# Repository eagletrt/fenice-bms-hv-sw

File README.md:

# Fenice's High Voltage Battery Management System

This branch contains two projects: mainboard and cellboard.

For guidelines on how this branching system works head over to the [master's branch README](https://github.com/eagletrt/fenice-bms-hv/blob/master/README.md#repo-guidlines).

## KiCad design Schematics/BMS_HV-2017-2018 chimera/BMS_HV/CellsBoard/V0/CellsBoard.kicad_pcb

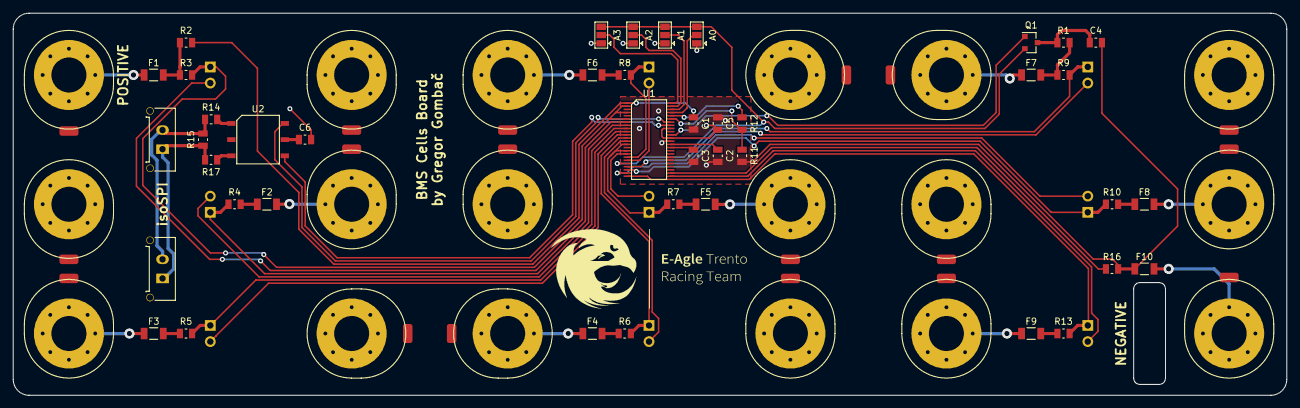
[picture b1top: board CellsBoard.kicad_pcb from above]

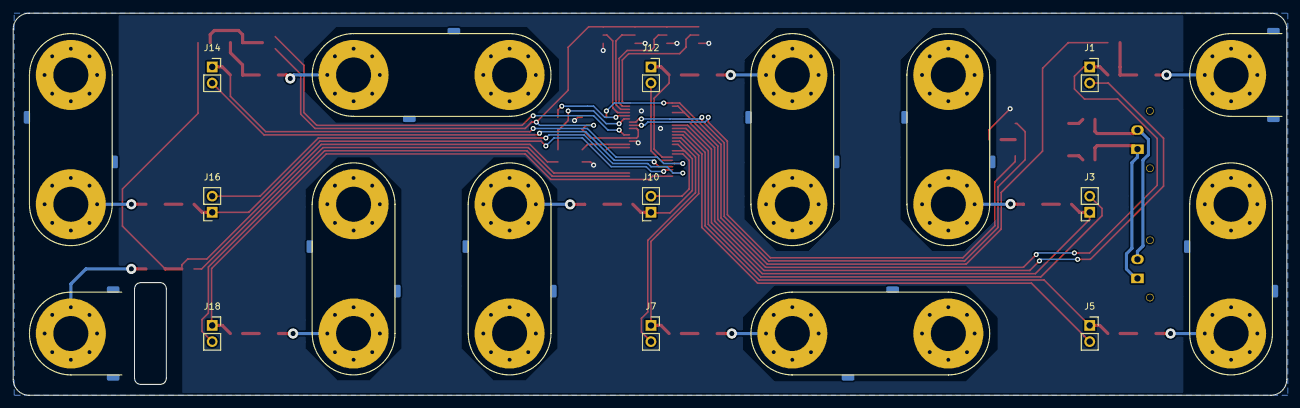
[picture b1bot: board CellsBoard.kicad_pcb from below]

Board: 2 copper layers, 200.0 x 60.0 mm, 61 parts (9 on the bottom side), 58 nets.

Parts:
C1, C4, C5: 100n; C_0805_2012Metric
C2, C3: 1u; C_0805_2012Metric
C6: 27p; C_0805_2012Metric
F1, F2, F3, F4, F5, F6, F7, F8, F9, F10: Fuse; Fuse_1206_3216Metric
J1: Temp9; PinSocket_1x02_P2.54mm_Vertical
J2: Cell9; CellEndS
J3: Temp8; PinSocket_1x02_P2.54mm_Vertical
J4: Cell8; CellShort
J5: Temp7; PinSocket_1x02_P2.54mm_Vertical
J6: Cell7; CellShort
J7: Temp6; PinSocket_1x02_P2.54mm_Vertical
J8: Cell6; CellLong
J10: Temp5; PinSocket_1x02_P2.54mm_Vertical
J11: Cell5; CellShort
J12: Temp4; PinSocket_1x02_P2.54mm_Vertical
J13: Cell4; CellShort
J14: Temp3; PinSocket_1x02_P2.54mm_Vertical
J15: Cell3; CellLong
J16: Temp2; PinSocket_1x02_P2.54mm_Vertical
J17: Cell2; CellShort
J18: Temp1; PinSocket_1x02_P2.54mm_Vertical
J19: Cell1; CellShort
J20: Cell0; CellEndD
J21, J22: isoSPI; Molex_Micro-Fit_3.0_43650-0215_1x02_P3.00mm_Vertical
JP1: A3; SolderJumper-3_P1.3mm_Open_Pad1.0x1.5mm
JP2: A2; SolderJumper-3_P1.3mm_Open_Pad1.0x1.5mm
JP3: A1; SolderJumper-3_P1.3mm_Open_Pad1.0x1.5mm
JP4: A0; SolderJumper-3_P1.3mm_Open_Pad1.0x1.5mm
Q1: BC846AW; SOT-23
R1, R2: 100R; R_0805_2012Metric
R3, R4, R5, R6, R7, R8, R9, R10, R13, R16: 330R; R_0805_2012Metric
R11: 1K4; R_0805_2012Metric
R12: 604R; R_0805_2012Metric
R14, R17: 22R; R_0805_2012Metric
R15: 120R; R_0805_2012Metric
U1: LTC6804; SSOP-48
U2: HM2103

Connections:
/0V: C1.2, C2.2, C3.2, C4.2, C5.2, C6.1, F10.2, JP1.1, JP2.1, JP3.1, JP4.1, R11.2, R16.1, U1.30, U1.31, U1.36
/A0: JP4.2, U1.45
/A1: JP3.2, U1.46
/A2: JP2.2, U1.47
/A3: JP1.2, U1.48
/C0: R16.2, U1.26
/C1: J18.1, R13.2, U1.24
/C2: J16.1, R10.2, U1.22
/C3: J14.1, R9.2, U1.20
/C4: J12.1, R8.2, U1.18
/C5: J10.1, R7.2, U1.14, U1.16
/C6: J7.1, R6.2, U1.12
/C7: J5.1, R5.2, U1.10
/C8: J3.1, R4.2, U1.8
/C9: J1.1, R3.2, U1.2, U1.4, U1.6
/CB1: F9.2, R13.1
/CB2: F8.2, R10.1
/CB3: F7.2, R1.1, R9.1
/CB4: F6.2, R8.1
/CB5: F5.2, R7.1
/CB6: F4.2, R6.1
/CB7: F3.2, R5.1
/CB8: F2.2, R4.1
/CB9: F1.2, R2.1, R3.1
/S1: J18.2, U1.25
/S2: J16.2, U1.23
/S3: J14.2, U1.21
/S4: J12.2, U1.19
/S5: J10.2, U1.17
/S6: J7.2, U1.13
/S7: J5.2, U1.11
/S8: J3.2, U1.9
/S9: J1.2, U1.7
/V+: C1.1, R2.2, U1.1
/VRef1: C2.1, U1.35
/VRef2: C3.1, U1.34
/Vreg: C5.1, JP1.3, JP2.3, JP3.3, JP4.3, Q1.2, U1.37, U1.40
/drive: Q1.1, U1.38
unnamed: C4.1, Q1.3, R1.2
unnamed: C6.2, U2.5
unnamed: F1.1, J2.1
unnamed: F2.1, J4.1
unnamed: F3.1, J6.1
unnamed: F4.1, J8.1
unnamed: F5.1, J11.1
unnamed: F6.1, J13.1
unnamed: F7.1, J15.1
unnamed: F8.1, J17.1
unnamed: F9.1, J19.1
unnamed: F10.1, J20.1
unnamed: J21.1, J22.1, R15.2, R17.2
unnamed: J21.2, J22.2, R14.2, R15.1
unnamed: R11.1, R12.2, U1.43
unnamed: R12.1, U1.44
unnamed: R14.1, U2.1
unnamed: R17.1, U2.3
unnamed: U1.41, U2.4
unnamed: U1.42, U2.6

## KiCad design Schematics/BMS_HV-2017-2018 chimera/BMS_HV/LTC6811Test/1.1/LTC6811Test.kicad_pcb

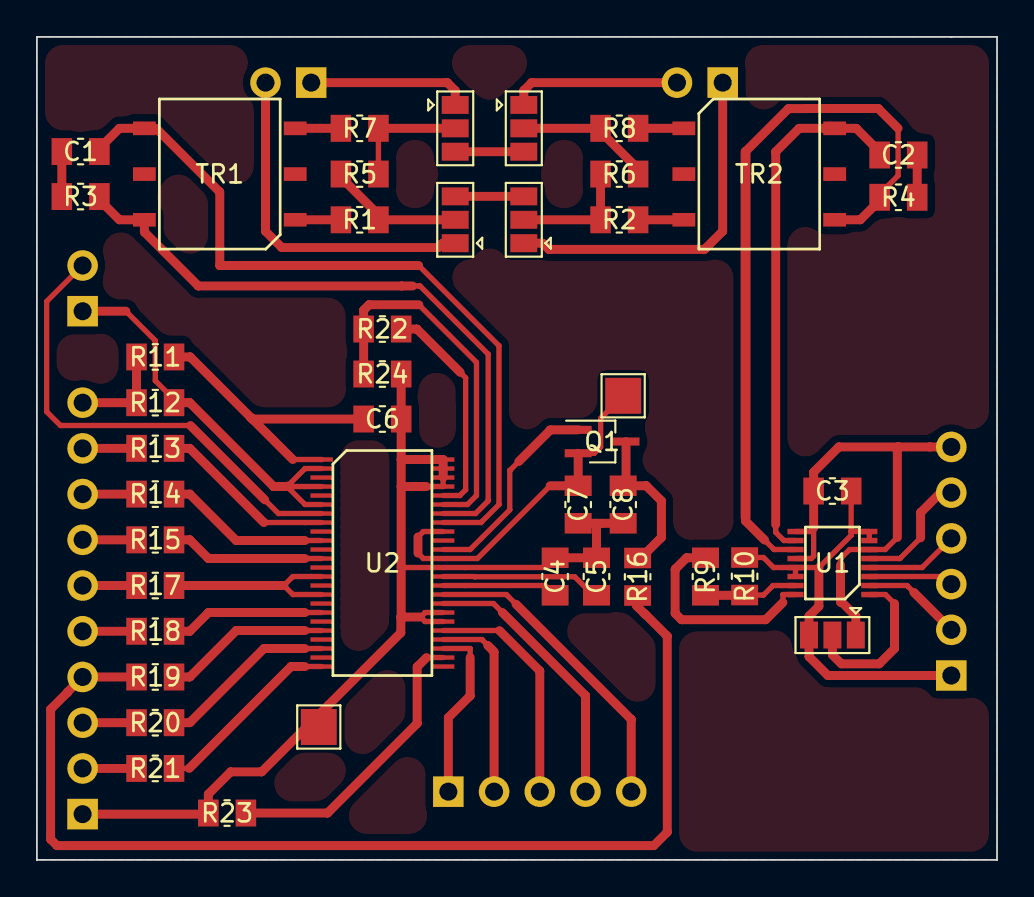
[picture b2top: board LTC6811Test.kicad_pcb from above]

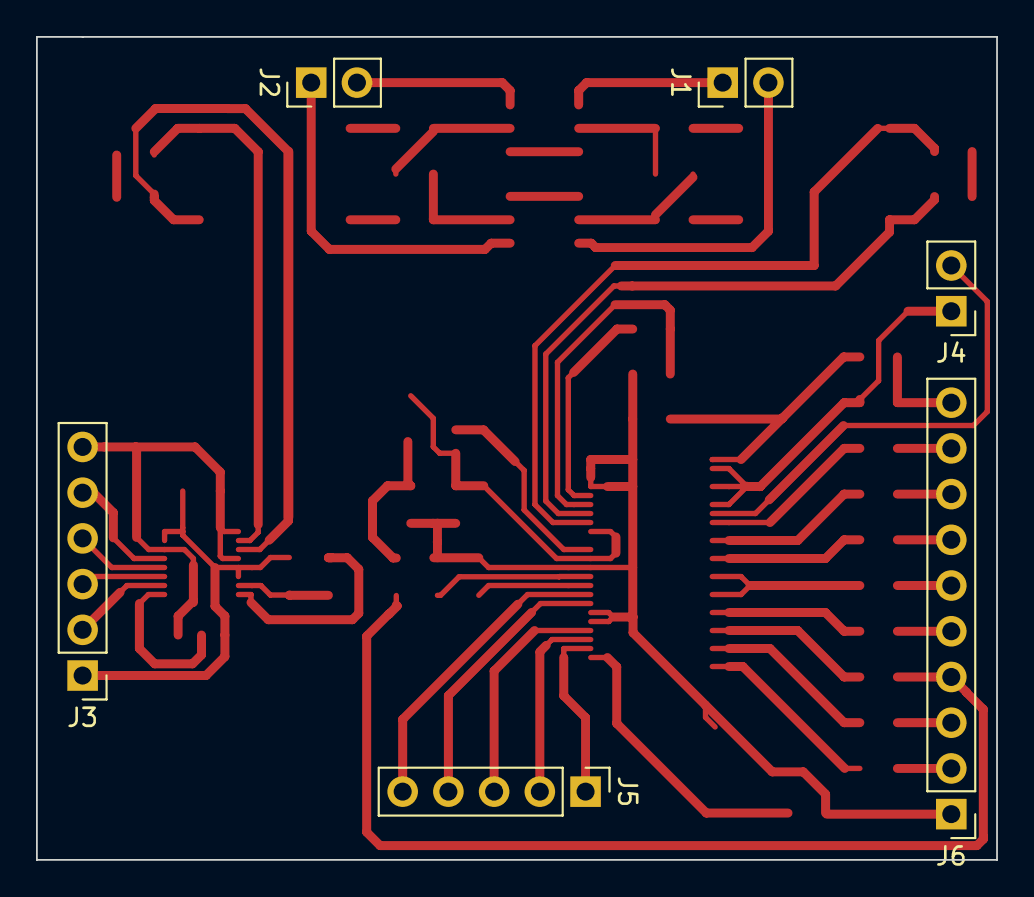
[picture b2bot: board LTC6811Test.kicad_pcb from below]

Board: 2 copper layers, 53.3 x 45.7 mm, 48 parts (6 on the bottom side), 63 nets.

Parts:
C1, C2: 15p; C_0805_2012Metric_Pad1.15x1.50mm_HandSolder
C3, C6, C7, C8: 100n; C_0805_2012Metric_Pad1.15x1.50mm_HandSolder
C4, C5: 1u; C_0805_2012Metric_Pad1.15x1.50mm_HandSolder
J1: IsoSPI_B_Conn; PinHeader_1x02_P2.54mm_Vertical
J2: IsoSPI_M_Conn; PinHeader_1x02_P2.54mm_Vertical
J3: Conn_01x06; PinHeader_1x06_P2.54mm_Vertical
J4: Temp_Conn; PinHeader_1x02_P2.54mm_Vertical
J5: GPIO_Conn; PinHeader_1x05_P2.54mm_Vertical
J6: Battery_Conn; PinHeader_1x10_P2.54mm_Vertical
JP1, JP2, JP3, JP4: IsoSPI_JP; SolderJumper-3_P1.3mm_Open_Pad1.0x1.5mm
JP5: EN_SolderJP; SolderJumper-3_P1.3mm_Open_Pad1.0x1.5mm
Q1: BC846AW; SOT-323_SC-70_Handsoldering
R1, R2, R7, R8: 22; R_0805_2012Metric_Pad1.15x1.50mm_HandSolder
R3, R4: 402; R_0805_2012Metric_Pad1.15x1.50mm_HandSolder
R5, R6, R11, R16: 100; R_0805_2012Metric_Pad1.15x1.50mm_HandSolder
R9, R22: 604; R_0805_2012Metric_Pad1.15x1.50mm_HandSolder
R10, R24: 1.4K; R_0805_2012Metric_Pad1.15x1.50mm_HandSolder
R12, R13, R14, R15, R17, R18, R19, R20, R21, R23: 330; R_0805_2012Metric_Pad1.15x1.50mm_HandSolder
TR1, TR2: HM2101NL
U1: LTC6820; MSOP-16
U2: LTC6811-2; SSOP-48

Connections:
+BATT: J6.10, R11.1, R12.1
-BATT: C4.1, C5.1, C6.1, C7.1, C8.2, J6.1, R23.1, R24.2, U2.30, U2.31, U2.36, U2.45, U2.46, U2.47, U2.48
/CS: J3.5, U1.5
/IM+: R4.1, TR2.4, U1.11
/IM-: C2.1, TR2.6, U1.10
/IsoSPI+: JP1.3, JP2.3
/IsoSPI-: JP3.3, JP4.3
/MISO: J3.3, U1.3
/MOSI: J3.2, U1.2
/MonitoringIC/Cell1: J6.2, R21.1
/MonitoringIC/Cell2: J6.3, R20.1
/MonitoringIC/Cell3: J6.4, R16.2, R19.1
/MonitoringIC/Cell4: J6.5, R18.1
/MonitoringIC/Cell5: J6.6, R17.1
/MonitoringIC/Cell6: J6.7, R15.1
/MonitoringIC/Cell7: J6.8, R14.1
/MonitoringIC/Cell8: J6.9, R13.1
/MonitoringIC/IS+: R3.1, TR1.6, U2.42
/MonitoringIC/IS-: C1.1, TR1.4, U2.41
/MonitoringIC/V+: C6.2, R11.2, U2.1
/MonitoringIC/VReg: C7.2, Q1.2, U2.37, U2.40
/SCK: J3.4, U1.4
GND: C3.2, J3.1, JP5.3, R10.2, U1.7, U1.8, U1.13, U1.14
unnamed: C1.2, R3.2
unnamed: C2.2, R4.2
unnamed: C4.2, U2.34
unnamed: C5.2, U2.35
unnamed: C8.1, Q1.3, R16.1
unnamed: J1.1, JP3.1
unnamed: J1.2, JP1.1
unnamed: J2.1, JP2.1
unnamed: J2.2, JP4.1
unnamed: J4.1, R12.2, U2.2, U2.4, U2.6
unnamed: J4.2, U2.7
unnamed: J5.1, U2.27
unnamed: J5.2, U2.28
unnamed: J5.3, U2.29
unnamed: J5.4, U2.32
unnamed: J5.5, U2.33
unnamed: JP1.2, R1.1, R5.1
unnamed: JP2.2, R2.2, R6.1
unnamed: JP3.2, R5.2, R7.1
unnamed: JP4.2, R6.2, R8.2
unnamed: JP5.2, U1.1
unnamed: Q1.1, U2.38
unnamed: R1.2, TR1.1
unnamed: R2.1, TR2.3
unnamed: R7.2, TR1.3
unnamed: R8.1, TR2.1
unnamed: R9.1, U1.16
unnamed: R9.2, R10.1, U1.15
unnamed: R13.2, U2.8
unnamed: R14.2, U2.10
unnamed: R15.2, U2.12
unnamed: R17.2, U2.14, U2.16
unnamed: R18.2, U2.18
unnamed: R19.2, U2.20
unnamed: R20.2, U2.22
unnamed: R21.2, U2.24
unnamed: R22.1, U2.44
unnamed: R22.2, R24.1, U2.43
unnamed: R23.2, U2.26
VDD: C3.1, J3.6, JP5.1, U1.6, U1.9, U1.12

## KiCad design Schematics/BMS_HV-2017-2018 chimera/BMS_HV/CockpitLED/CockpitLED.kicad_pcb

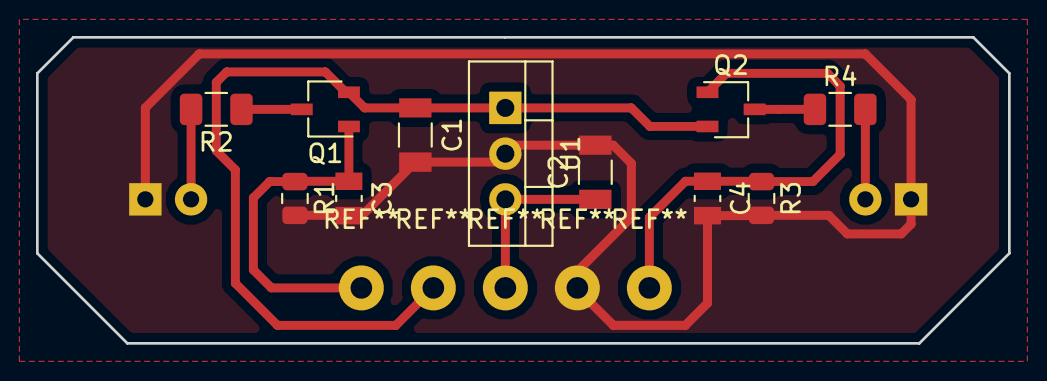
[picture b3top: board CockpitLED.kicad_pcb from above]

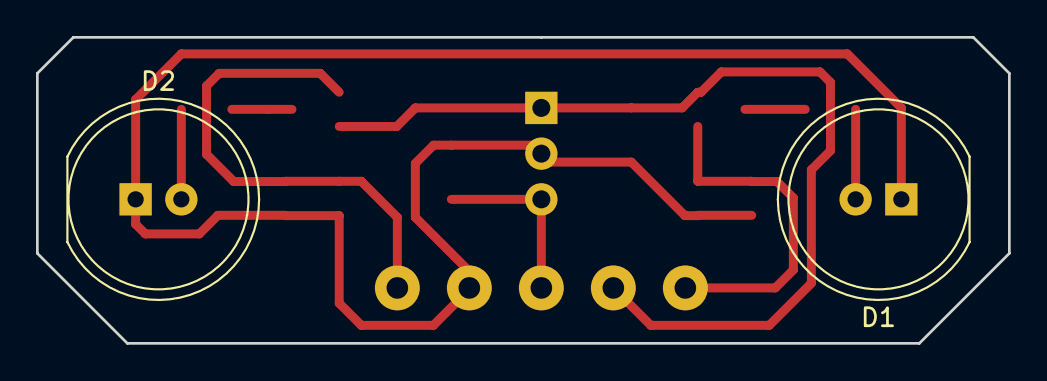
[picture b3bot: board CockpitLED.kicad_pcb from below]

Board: 2 copper layers, 54.0 x 17.0 mm, 13 parts (2 on the bottom side), 9 nets.

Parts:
C1: 10u; C_1206_3216Metric
C2: 22u; C_1206_3216Metric
C3, C4: 100n; C_0805_2012Metric
D1, D2: SSL-LX100133SRC/E; LED_D10.0mm
Q1, Q2: TSM3401; TSOT-23
R1, R3: 1M; R_0805_2012Metric
R2, R4: 330; R_1206_3216Metric
U1: VXO7805-500; TO-220-3_Vertical

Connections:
+5V: C2.1, U1.3
+12V: C1.1, Q1.2, Q2.2, U1.1
/BMS: C4.1, Q2.1, R3.1
/IMD: C3.1, Q1.1, R1.1
GND: C1.2, C2.2, C3.2, C4.2, D1.1, D2.1, R1.2, R3.2, U1.2
unnamed: D1.2, R2.2
unnamed: D2.2, R4.2
unnamed: Q1.3, R2.1
unnamed: Q2.3, R4.1

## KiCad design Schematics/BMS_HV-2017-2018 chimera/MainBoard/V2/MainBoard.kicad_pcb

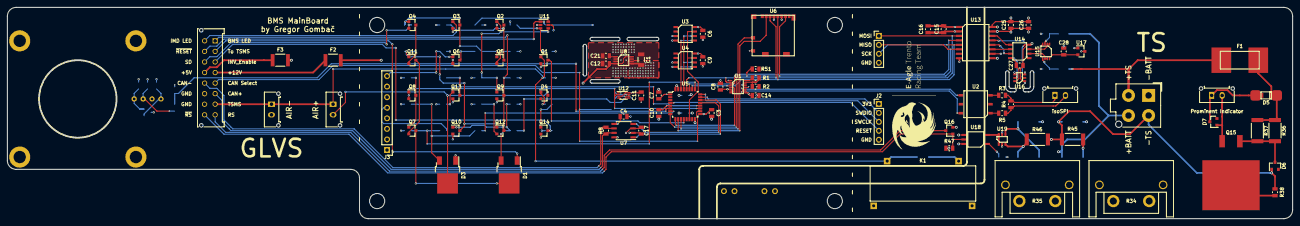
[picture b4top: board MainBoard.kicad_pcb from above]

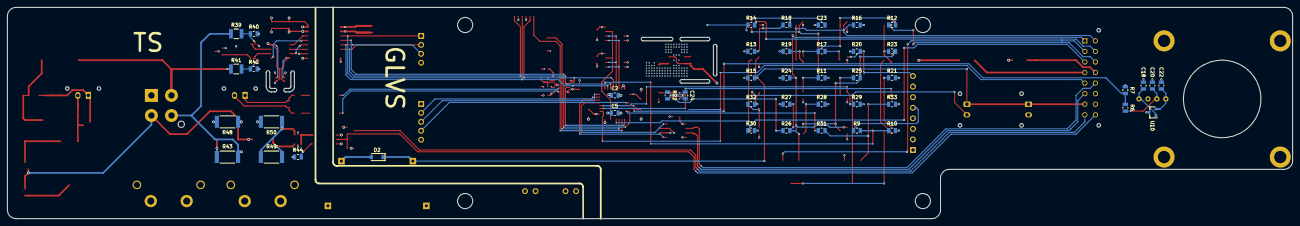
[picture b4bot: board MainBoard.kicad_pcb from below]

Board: 4 copper layers, 365.0 x 60.0 mm, 133 parts (45 on the bottom side), 98 nets.

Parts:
C1: 47u; C_1206_3216Metric
C2, C12: 4.7u; C_0805_2012Metric
C3, C4, C7, C11, C15, C17, C26, C28: 100n; C_0805_2012Metric
C5, C23, C27: 1u; C_0805_2012Metric
C6, C8, C9, C10, C14, C21, C24: 10n; C_0805_2012Metric
C16, C25: 10u; C_0805_2012Metric
C18, C22: 47n; C_0805_2012Metric
C20: 4.7n; C_0805_2012Metric
D1, D3: BT150S-600R; TO-252-2
D2: BAS16GW; D_SOD-123
D4, D6, D7: MMBZ4624; D_SOT-23_ANK
D5: BZD27C56P; DO-219AB
F1: 0885001.DR; SMD_Fuse
F2, F3: 0ZCG 2A; Fuse_1812_4532Metric
J1: isoSPI; Molex_Micro-Fit_3.0_43650-0215_1x02_P3.00mm_Vertical
J2: SWDebug; PinHeader_1x05_P2.54mm_Vertical
J3: IMD; PinHeader_1x08_P3mm_Vertical
J4: IO; Molex_Micro-Fit_3.0_43045-1612_2x08_P3.00mm_Vertical
J5: AIR-; Molex_Micro-Fit_3.0_43650-0215_1x02_P3.00mm_Vertical
J6: AIR+; Molex_Micro-Fit_3.0_43650-0215_1x02_P3.00mm_Vertical
J7: ProminentIndicator; Molex_Micro-Fit_3.0_43650-0215_1x02_P3.00mm_Vertical
J8: HV; Molex_Mega-Fit_76829-0104_2x02_P5.70mm_Vertical
J9: IMD_TS+; PinHeader_1x02_P3mm_Vertical
J10: IMD_TS-; PinHeader_1x02_P3mm_Vertical
K1: KT12-1A; KT_THT
Q1, Q5, Q6, Q12: TSM2306; SOT-23
Q2, Q3, Q4, Q7, Q9, Q10, Q11: TSM3401; SOT-23
Q8, Q13, Q16: TSM2312; SOT-23
Q14: BC846AW; SOT-23
Q15: BULB49D; D2PAK
R1: 604; R_0805_2012Metric
R2: 1.4K; R_0805_2012Metric
R3, R5: 22; R_0805_2012Metric
R4: 100; R_0805_2012Metric
R6, R7, R16, R17, R18, R19, R24, R25, R28: 10K; R_0805_2012Metric
R8: 120; R_0805_2012Metric
R9: 1.6K; R_0805_2012Metric
R10: 590; R_0805_2012Metric
R11, R14, R15, R21, R22, R27, R29, R33, R47: 100K; R_0805_2012Metric
R12, R23: 1M; R_0805_2012Metric
R13: 220K; R_0805_2012Metric
R20: 2K2; R_0805_2012Metric
R26, R31: 3.3K; R_0805_2012Metric
R30, R51: 1K; R_0805_2012Metric
R32: 22K; R_0805_2012Metric
R34, R35: 10K; TO-247_wHeatsink
R36, R37: 390K; R_2512_6332Metric
R38: 330; R_0805_2012Metric
R39, R41: 10M; R_1210_3225Metric
R40: 71K5; R_0805_2012Metric
R42: 34K8; R_0805_2012Metric
R43, R48: 100M; R_2512_6332Metric
R44: 470; R_0805_2012Metric
R45: 10M; R_2512_6332Metric
R46: 1G; R_2512_6332Metric
R49, R50: 2.2M; R_2512_6332Metric
U1: LTC6820; MSOP-16
U2: HM2103
U3, U4: M24M02; SON-8
U5: STM32F334K8; LQFP-32_7x7mm_P0.8mm
U6: MicroSD; Molex_MicroSD_PushPull
U7: MCP2562; SOIC-8_3.9x4.9mm_P1.27mm
U8: LP2989; SOIC-8
U9: HTFS200-P; HTFS 200-P
U10: REF2920; SOT-23
U11: MAX16053; SOT-23-6
U12: SN74LVC1G123; VSSOP-8_2.3x2mm_P0.5mm
U13: ISOW7841; SOIC-16
U14: LTC1865L; SON-8
U15: LTC6259; MSOP-8
U16: REF3433; SOT-23-6
U17: REF2940; SOT-23
U18: FODM611
U19: TPS3700; SOT-23-6

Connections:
+3V3: C1.1, C2.1, C3.1, C4.1, C5.1, C6.1, C7.1, C8.1, C9.1, C10.1, C11.1, C15.1, C16.1, J2.1, R14.1, R22.2, R51.2, U1.6, U3.8, U4.3, U4.8, U5.1, U5.5, U5.17, U6.4, U7.5, U8.5, U8.6, U12.3, U12.8, U13.1
+5V: C12.1, C14.1, C17.1, C18.1, F3.1, U1.9, U1.12, U7.3, U8.4, U8.8, U9.1, U10.1, U18.6
+12V: F2.2, J3.2, Q2.2, Q3.2, Q9.2, Q10.2, R11.1, R13.1, R16.2, R21.2, R24.2, R30.1, U11.5
+BATT: J8.4, K1.3, R39.2, R43.1
+TS: F1.1, J8.3, J9.1, J9.2, R34.2, R35.2, R41.2, R43.2, R45.1
-BATT: C25.2, C26.2, C27.2, C28.2, J8.1, R40.2, R42.2, R48.2, R50.1, U13.9, U13.15, U14.4, U15.4, U16.1, U16.2, U17.3, U19.2
-TS: D6.2, J8.2, J10.1, J10.2, R38.2, R45.2, R46.2, R48.1
/6820: U1.5, U5.9
/BMS_Fault: Q13.1, R29.1, U5.20
/CAN+: J4.6, R8.2, U7.7
/CAN-: J4.13, R8.1, U7.6
/CANS: J4.5, U5.18
/CD: U5.11, U6.9
/Current: C20.1, R6.1, U9.3
/HV/3V3ISO: C27.1, U14.8, U16.5, U16.6
/HV/4VISO: C28.1, U15.8, U17.2
/HV/5VISO: C25.1, C26.1, R44.1, U13.10, U13.16, U16.3, U16.4, U17.1, U19.5
/HV/PackV: U14.3, U15.1, U15.2
/HV/TSV: U14.2, U15.6, U15.7
/I+: U1.11, U2.4
/I-: U1.10, U2.6
/IBIAS: R1.2, U1.16
/ICMP: R1.1, R2.2, U1.15
/IMD: R9.2, R10.1, U5.25
/IMD_Fault: J3.8, Q6.1, R20.1
/MISO: R51.1, U1.3, U5.27, U6.7, U13.6
/MOSI: U1.2, U5.28, U6.3, U13.3
/PADC: U5.8, U13.4
/PC_Ended: R31.2, U5.7
/RST: J2.4, U5.4
/SCK: U1.4, U5.26, U6.5, U13.5
/SCL: U3.6, U4.6, U5.29
/SDA: U3.5, U4.5, U5.30
/SDCard: U5.10, U6.2
/SD_Status: Q1.3, U5.12
/SWCLK: J2.3, U5.24
/SWDIO: J2.2, U5.23
/Shutdown/BMS_SD: Q7.2, Q11.3
/Shutdown/IMD_SD: Q4.3, Q11.2, R23.2
/Shutdown/~RESET: Q2.1, Q9.1, R11.2, U11.4
/TS_ON: Q8.1, U5.19, U12.2
/WC: U3.7, U4.7, U5.14
/isoSPI+: J1.1, R3.1, R4.2
/isoSPI-: J1.2, R4.1, R5.1
BMS_LED: J4.1, Q9.3, Q10.1, Q12.3, R24.1
From_SD: J4.11, Q4.2, R12.2
From_TSMS: D2.1, J4.7, J5.1, J6.1, K1.1, Q1.1, R15.1
GND: C1.2, C2.2, C3.2, C4.2, C5.2, C6.2, C7.2, C8.2, C9.2, C10.2, C11.2, C12.2, C14.2, C15.2, C16.2, C17.2, C18.2, C20.2, C21.2, C22.2, C23.2, D2.2, D3.1, J2.5, J3.1, J3.3, J3.4, J4.14, J4.15, J5.2, K1.2, Q1.2, Q6.2, Q8.2, Q13.2, Q14.2, Q16.2, R2.1, R7.1, R10.2, R15.2, R18.2, R19.1, R20.2, R27.2, R28.1, R29.2, R33.2, R47.2, U1.1, U1.7, U1.8, U1.13, U1.14, U3.3, U3.4, U4.4, U5.16, U5.31, U5.32, U6.6, U6.10, U7.2, U7.8, U8.3, U9.2, U10.3, U11.2, U12.1, U12.4, U13.2, U13.8, U18.4
IMD_LED: J4.9, Q2.3, Q3.1, Q5.3, R16.1
INV_Enable: J4.3, Q14.3, R30.2
NRelayStat: J4.16, Q16.1, R47.1, U18.5
unnamed: C21.1, U8.1
unnamed: C22.1, U9.4, U10.2
unnamed: C23.1, U11.6
unnamed: C24.1, R22.1, U12.7
unnamed: C24.2, U12.6
unnamed: D1.2, Q7.3
unnamed: D1.3, R26.1, R27.1
unnamed: D3.2, D4.1, J6.2
unnamed: D3.3, R31.1, R33.1
unnamed: D4.2, R32.2
unnamed: D5.1, D7.1, J7.1
unnamed: D5.2, F1.2, R36.1, R37.1
unnamed: D6.1, Q15.1, R36.2, R37.2
unnamed: D7.2, J7.2, Q15.2
unnamed: F2.1, J4.4
unnamed: F3.2, J4.12
unnamed: J3.5, R9.1
unnamed: K1.4, R34.1, R35.1
unnamed: Q3.3, Q4.1, Q5.1, R12.1, R17.1
unnamed: Q5.2, R19.2
unnamed: Q6.3, R17.2
unnamed: Q7.1, Q8.3, R21.1
unnamed: Q10.3, Q11.1, Q12.1, R23.1, R25.1
unnamed: Q12.2, R28.2
unnamed: Q13.3, R25.2
unnamed: Q14.1, R32.1
unnamed: Q15.3, R38.1
unnamed: R3.2, U2.3
unnamed: R5.2, U2.1
unnamed: R6.2, R7.2, U5.6
unnamed: R13.2, R18.1, U11.3
unnamed: R26.2, U12.5
unnamed: R39.1, R40.1, U15.3
unnamed: R41.1, R42.1, U15.5
unnamed: R44.2, U18.1
unnamed: R46.1, R49.1, U19.3
unnamed: R49.2, R50.2, U19.4
unnamed: U5.21, U7.4
unnamed: U5.22, U7.1
unnamed: U13.11, U14.6
unnamed: U13.12, U14.7
unnamed: U13.13, U14.1
unnamed: U13.14, U14.5
unnamed: U18.3, U19.1, U19.6
RESET_BUTTON: J4.10, R14.2, U11.1
RelayStat: J4.8, Q16.3
To_TSMS: D1.1, J4.2

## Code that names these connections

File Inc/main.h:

/* USER CODE BEGIN Header */
/**
 * @file		main.h
 *
 * @date		Oct 9, 2019
 *
 * @author		Matteo Bonora [matteo.bonora@studenti.unitn.it]
 * @author		Simone Ruffini [simone.ruffini@studenti.unitn.it]
 */
/* USER CODE END Header */

/* Define to prevent recursive inclusion -------------------------------------*/
#ifndef __MAIN_H
#define __MAIN_H

#ifdef __cplusplus
extern "C" {
#endif

/* Includes ------------------------------------------------------------------*/
#include "stm32g4xx_hal.h"

/* Private includes ----------------------------------------------------------*/
/* USER CODE BEGIN Includes */
#include "error/error.h"
#include "pack.h"
#include "stm32g4xx_ll_usart.h"
/* USER CODE END Includes */

/* Exported types ------------------------------------------------------------*/
/* USER CODE BEGIN ET */

/* USER CODE END ET */

/* Exported constants --------------------------------------------------------*/
/* USER CODE BEGIN EC */

/* USER CODE END EC */

/* Exported macro ------------------------------------------------------------*/
/* USER CODE BEGIN EM */

/* USER CODE END EM */

/* Exported functions prototypes ---------------------------------------------*/
void Error_Handler(void);

/* USER CODE BEGIN EFP */
void check_timers();
void read_volts();
void read_temps();
/* USER CODE END EFP */

/* Private defines -----------------------------------------------------------*/
#define ANALOG_DATA_Pin GPIO_PIN_13
#define ANALOG_DATA_GPIO_Port GPIOC
#define IP_LOW_Pin GPIO_PIN_14
#define IP_LOW_GPIO_Port GPIOC
#define IP_HIGH_Pin GPIO_PIN_15
#define IP_HIGH_GPIO_Port GPIOC
#define CS_EEPROM_Pin GPIO_PIN_0
#define CS_EEPROM_GPIO_Port GPIOF
#define CARD_INSERT_Pin GPIO_PIN_1
#define CARD_INSERT_GPIO_Port GPIOF
#define MUX_A2_Pin GPIO_PIN_0
#define MUX_A2_GPIO_Port GPIOA
#define MUX_A3_Pin GPIO_PIN_1
#define MUX_A3_GPIO_Port GPIOA
#define CS_LTC_Pin GPIO_PIN_4
#define CS_LTC_GPIO_Port GPIOA
#define ADC_SIN_Pin GPIO_PIN_0
#define ADC_SIN_GPIO_Port GPIOB
#define MUX_A1_Pin GPIO_PIN_1
#define MUX_A1_GPIO_Port GPIOB
#define MUX_A0_Pin GPIO_PIN_2
#define MUX_A0_GPIO_Port GPIOB
#define CS_SD_Pin GPIO_PIN_12
#define CS_SD_GPIO_Port GPIOB
#define BMS_FAULT_Pin GPIO_PIN_9
#define BMS_FAULT_GPIO_Port GPIOA
#define TS_ON_Pin GPIO_PIN_10
#define TS_ON_GPIO_Port GPIOA
#define PC_ENDED_Pin GPIO_PIN_11
#define PC_ENDED_GPIO_Port GPIOA
#define PWM_IMD_Pin GPIO_PIN_12
#define PWM_IMD_GPIO_Port GPIOA
#define HOLD_Pin GPIO_PIN_15
#define HOLD_GPIO_Port GPIOA
#define CHARGE_Pin GPIO_PIN_5
#define CHARGE_GPIO_Port GPIOB
#define LED_2_Pin GPIO_PIN_6
#define LED_2_GPIO_Port GPIOB
#define LED_1_Pin GPIO_PIN_7
#define LED_1_GPIO_Port GPIOB
/* USER CODE BEGIN Private defines */

/* USER CODE END Private defines */

#ifdef __cplusplus
}
#endif

#endif /* __MAIN_H */

/************************ (C) COPYRIGHT STMicroelectronics *****END OF FILE****/

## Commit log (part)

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2022-03-31 cellboards: fixes
2022-04-05 cellboards: enabled automatic retransmittion and added 1ms delay between multiple can packets
2022-04-06 updated microlibs
2022-04-06 cellboard: added async blinking
2022-04-06 cellboard: implemented check on automatic retransmittion
2022-04-06 cellboard: fixed blinking on cell 0
2022-04-06 cellboard: implemented measurements flag as bitset and added ts_status sending message to 200ms timer (with temps)
2022-04-06 cellboard: fixed (again) index_blink
2022-04-11 adc124s: little fix for fpu performance improvement
2022-04-11 can: moved handle defines to mainboard_config.h
2022-04-11 measures: implemented flag-based timing
2022-04-11 adaptations to new board
2022-04-11 error: added feedback_circuitry error
2022-04-11 cli_bms: added feedbacks and can_forward commands
2022-04-11 bms_fsm: adapted to new feedback system
2022-04-11 fixed feedbacks enum
2022-04-11 added measures flags checking in main loop
2022-04-12 updated can-cicd to bbba249
2022-04-22 cellboard: fixes
2022-04-22 updated micro-libs
2022-04-22 cellboard: using micro-libs/timer-utills
2022-04-27 cellboard: fixed balancing discharge
2022-04-27 pack: ordered things up
2022-04-27 fans_buzzer: added control for fans (and buzzer)
2022-04-27 enum names changed
2022-04-27 bms_fsm: fixed fault state exit condition
2022-04-27 small fixes
2022-04-28 added watch cli command and coloured output for "volt all"
2022-05-02 config: fixed in order to avoid dynamic allocation
2022-05-09 added .gitattributes in order to run clang-format on .c and .h files
2022-05-09 cli: added colours and discharge info to "volt all"; fixed imd; made watch non stopping
2022-05-09 fenice_config: added discharge definitions
2022-05-09 bal: better control on end of discharge and added target voltage
2022-05-09 added dynamic cellboard distribution
2022-05-09 added timer
2022-05-09 soc: saving to eeprom every 5 seconds
2022-05-09 error: fixed error timing in order to accomplish the rules (take into account the communication time)
2022-05-09 modified
2022-05-09 fans: fixed fans initial speed
2022-05-09 applied clang-format to all files
2022-05-12 removed comment in comment causing warning
2022-05-13 can_comm: fixed can_x_send status return and modified CAN_WAIT
2022-05-13 added error checking
2022-06-10 can-cicd update(now only can)
2022-06-10 fixed typo
2022-06-10 implemented open wire check
2022-06-10 new canlib adaptations
2022-06-10 can update
2022-06-10 finished feedback system
2022-06-10 fixed missing things
2022-06-10 added pack low level control
2022-06-10 fixing everywhere
2022-06-14 updated canlib
2022-06-14 fixed CAN_WAIT
2022-06-14 error: fixed possible overflow on get_timeout_delta
2022-06-14 measures: increased message interval from 20 to 50 ms
2022-06-14 bms_fsm: fixed feedbacks checking
2022-06-14 can_comm: removed CAN_WAIT macro
2022-06-14 bootloader docs
2022-06-14 fixed links
2022-06-16 updated submodules
2022-06-16 timebase: switched from measures to timebase and changed the timer functionality
2022-06-16 feedback: updated constants
2022-06-16 bms_fsm: fixed precharge trheshold and on state function
2022-06-16 reset on hard_fault
2022-06-16 cli_bms: improved volts functionality
2022-06-16 minor fixes
2022-06-16 can_comms: added shutdown_status message handling
2022-06-17 minor fixes and can update
2022-06-21 updated can
2022-06-21 changed all sprintf to snprintf
2022-06-23 implemented automatic fans speed based on temperature
2022-06-23 dynamically calculated shunt_offset at startup
2022-06-23 implemented soc (not the @Bonnee way <3)
2022-06-27 added HV_FANS_OVERRIDE logic
2022-07-06 updated docs
2022-07-06 docs: moved .pages in the right place
2022-07-14 fix: temp management
2022-07-21 working implementation running in Varano
2022-08-09 chore: updated submodules
2022-08-19 working in FSG
2022-08-30 fix: error handling in temps and voltages
2022-08-31 fix: fixed message cells_temp
2022-10-12 feat: implemented cancid version
2022-10-18 updated canlib and fixed compilation error with some compiler
2022-11-09 committino carino per carboncino: increased readability + fixed some misspellings and grammatical horrors
2022-11-09 #ccpc: increased readability of the mainboard's docs [next up: subsystems]
2023-02-15 Update LICENSE
2023-03-31 refactor: Mainboard initial code refactoring
2023-03-31 feat(max22530): Added MAX22530AWE+ communication functions
2023-04-01 docs(max22530): Added command structure to comments
2023-04-02 feat(pack): Internal voltage measurement with MAX22530
2023-04-14 fix(pack): changed adc port and pin
2023-04-24 feat(config): reafactored bms config files
2023-04-24 feat(error): initial bms errors implementation
2023-04-24 feat(pack): refactored voltage measurement functions
2023-04-24 feat(pack): refactored temperature measurement functions
2023-04-24 fix: small adjustment to the cubeMX project
2023-05-18 refactor: move cellboard code to mainboard
2023-05-20 refactor(cli_bms): refactor BMS CLI functions
2023-05-25 feat: add index get to cell voltage functions
2023-05-25 feat: incomplete code implementation
2023-05-31 feat: implement function for ADC MAX22530
2023-06-06 fix: canlib related fixes
2023-06-08 fix: update latest canlib changes
2023-06-13 docs: add docs section
2023-06-13 docs: fix flash the firmware section
2023-06-16 fix: small fixes
2023-06-16 fix: flash via can working
2023-06-17 feat: change internal voltage adc
2023-06-18 refactor(balancing): move balancing handling from mainboard to cellboard
2023-06-20 fix(docs): fix wrong url
2023-06-21 test: can communication ECU, volante, porco
2023-06-22 refactor: cellboard balancing
2023-06-25 feat: cellboard balancing
2023-06-26 feat: change multiplexer feedbacks
2023-06-27 fix: feedbacks and adc
2023-06-28 refactor: feedbacks, cell voltages and temperatures
2023-06-28 fix: fans pwm
2023-06-28 feat: functions for testing + small fixes
2023-06-29 fix: flash via can and errors
2023-06-29 fix: wrong voltages readings and conversion
2023-07-01 fix: wrong temperature readings and feedbacks
2023-07-01 feat: first ts on :)
2023-07-01 feat: first real and stable ts on :D
2023-07-02 fix: feedbacks, temperatures and can
2023-07-03 fix: feedback timeout trigger after changing state
2023-07-03 feat: implement can watchdogs
2023-07-04 fix: comment watchdog in fsm for test
2023-07-04 fix: wait for feedbacks update on ts on
2023-07-04 fix: wrong feedback thresholds
2023-07-05 fix: balancing and wrong temperatures info
2023-07-05 fix: continuous balancing
2023-07-05 feat: partial new fsm implementation
2023-07-05 feat: improve feedbacks
2023-07-05 feat: new fsm implementation ready for test
2023-07-05 feat: fms edge cases
2023-07-05 refactor: feedbacks randomly change values
2023-07-05 feat: first complete TS on :D
2023-07-05 fix: remove delay
2023-07-06 feat: mainboard watchdog implementation
2023-07-06 fix: slow cellboard CAN communication
2023-07-06 fix: check precharge pack and bus voltages
2023-07-08 fix: remove precharge feedback check in ts on status
2023-07-09 fix: disable watchdogs for handcart
2023-07-09 fix: init buffer to 0
2023-07-09 fix: feedback threshold for handcart
2023-07-09 feat: start fans on balancing
2023-07-09 feat: change fans speed based on balancing
2023-07-09 feat: change measure timer handling
2023-07-09 feat: new error implementation
2023-07-09 feat: new errors implementation
2023-07-10 fix: fault after car power on
2023-07-10 refactor: partial cli refactor
2023-07-10 fix: reset timestamp inside while
2023-07-10 feat: send info via CAN on FSM transition
2023-07-10 feat: change fans speed based on temperature always
2023-07-11 fix: volt readings and fans speed while balancing
2023-07-12 feat: fans controls
2023-07-13 fix: bms fault on power on
2023-07-19 feat: change old balancing FSM with the new version
2023-07-20 fix: new balancing FSM
2023-07-20 fix: cellboard_id check
2023-07-23 fix: set balancing threshold below the limit
2023-07-24 docs: add partial cellboard docs
2023-07-24 refactor: change measures check method
2023-07-24 fix: shorter air check timeout
2023-07-25 fix: send min, max and avg temp and volts one time
2023-07-25 fix: get correct current while charging
2023-07-25 feat: change fans curve
2023-07-26 fix: revert measurement code to previous version
2023-07-26 fix: correct balancing on time
2023-07-26 fix: balancing always off after cooldown start
2023-07-26 fix: send wrong discharge cells via CAN
2023-07-27 fix: wrong timer in autoreload set
2023-07-27 feat: get cells to discharge only during state transition
2023-08-01 feat: send fans speed via CAN
2023-08-01 fix: auto fans speed not working after override reset
2023-08-06 refactor: CAN communication in mainboard
2023-08-07 refactor: CAN communication in cellboard
2023-08-09 fix: fans and current connectors disconnection errors
2023-08-10 test: current connector disconnection
2023-08-10 fix: git sborato
2023-08-10 fix: errors sborat
2023-08-10 fix: wrong ids
2023-08-10 fix: current sensors connector errors
2023-08-10 fix: temperature connectors errors
2023-08-11 feat: add less strict temperatures error check
2023-08-15 fix: errors buffer overflow
2023-08-15 feat: disable temp check
2023-08-16 fix: switch from single to group temp error check
2023-09-22 fix: AMS on balancing
2023-09-29 fix: precharge error handling
2023-09-29 fix: battery voltage mismatch error
2023-10-02 feat(mainboard): new errors implementation
2023-10-03 feat(mainboard): move error instance name definition
2023-10-04 fix: small merge errors
2023-10-06 fix: init error before everithing
2023-10-07 feat(mainboard): ready for error testing
2023-10-10 refactor(mainboard): CAN communication
2023-10-10 feat: last can commit
2023-10-21 feat(error): send errors via can
2023-10-21 feat(feedbacks): send last saved feedbacks via CAN
2023-10-21 working on the car: 21st October
2023-10-21 feat(current): get average of multiples current values
2023-11-06 fix(mainboard): precharge timeout
2023-11-09 feat: update to last canlib version
2023-11-19 fix: power conversion in kW
2023-12-12 feat: set balancing threshold via can and send cell voltage sum and average
2023-12-13 fix: send cell voltages info via can
2023-12-13 fix: use sum of cells voltage in voltage mistmatch error check
2024-02-21 fix(current): remove shunt from current measures
2024-02-21 feat(blink): update led blink library to the latest version
2024-02-27 feat(balancing): remove eeprom blocking functions from can interrupt callback
2024-03-01 fix(precharge): increase precharge timeout
2024-03-06 feat(error): keep latest expired error
2024-03-06 feat(debug): add can debug messages
2024-03-06 feat(current): change current minimum threshold
2024-03-21 fix(debug-signals): set feedback signals only in ts on
2024-03-26 feat(errors): implemenet new error library
2024-04-04 feat: update canlib version
2024-04-06 fix: change check mux feedbacks low threshold
2024-04-11 fix: wrong filter id for cellboard balancing
2024-04-11 fix: cant stop balancing
2024-04-17 feat: update canlib and error-handler versions
2024-04-18 added check for lv discharge
2024-04-18 added check for battery handcart connection
2024-05-17 fixed logic condition for handcart connection inside bms_fms
2024-06-08 fix: change feedback thresholds for handcart
2024-07-12 fix(errors)move error_expire inside the correct timer callback
2024-07-15 fix(errors): error expire at random
2024-08-07 fix(temperatures): fix broken reading temperatures
2024-08-07 BREAKING: NEW ERROR LIBRARY
2024-08-07 fix(errors): wrong function in can_comm
2024-08-09 feat(canlib): Update canlib version
2024-08-17 fix: fsg 2024
2024-09-01 feat: remove debug message via CAN
2025-05-08 feat: update canlib to current version
2025-06-10 fix: flash cellboard 0 via can
2025-12-01 fix: lower precharge threshold
2025-12-01 fix: minor workarounds
2025-12-01 chore: update mainboard srec script
2025-12-01 fix: reserve additional section to mainboard bootloader
2026-06-28 fix: remove old submodules
2026-06-28 chore: add missing submodule
2026-06-28 fix: update cellboard with new canlib
2026-06-29 fix: update mainboard with new canlib
